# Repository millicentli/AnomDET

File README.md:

# AnomDET
Anomaly Detection @ UW

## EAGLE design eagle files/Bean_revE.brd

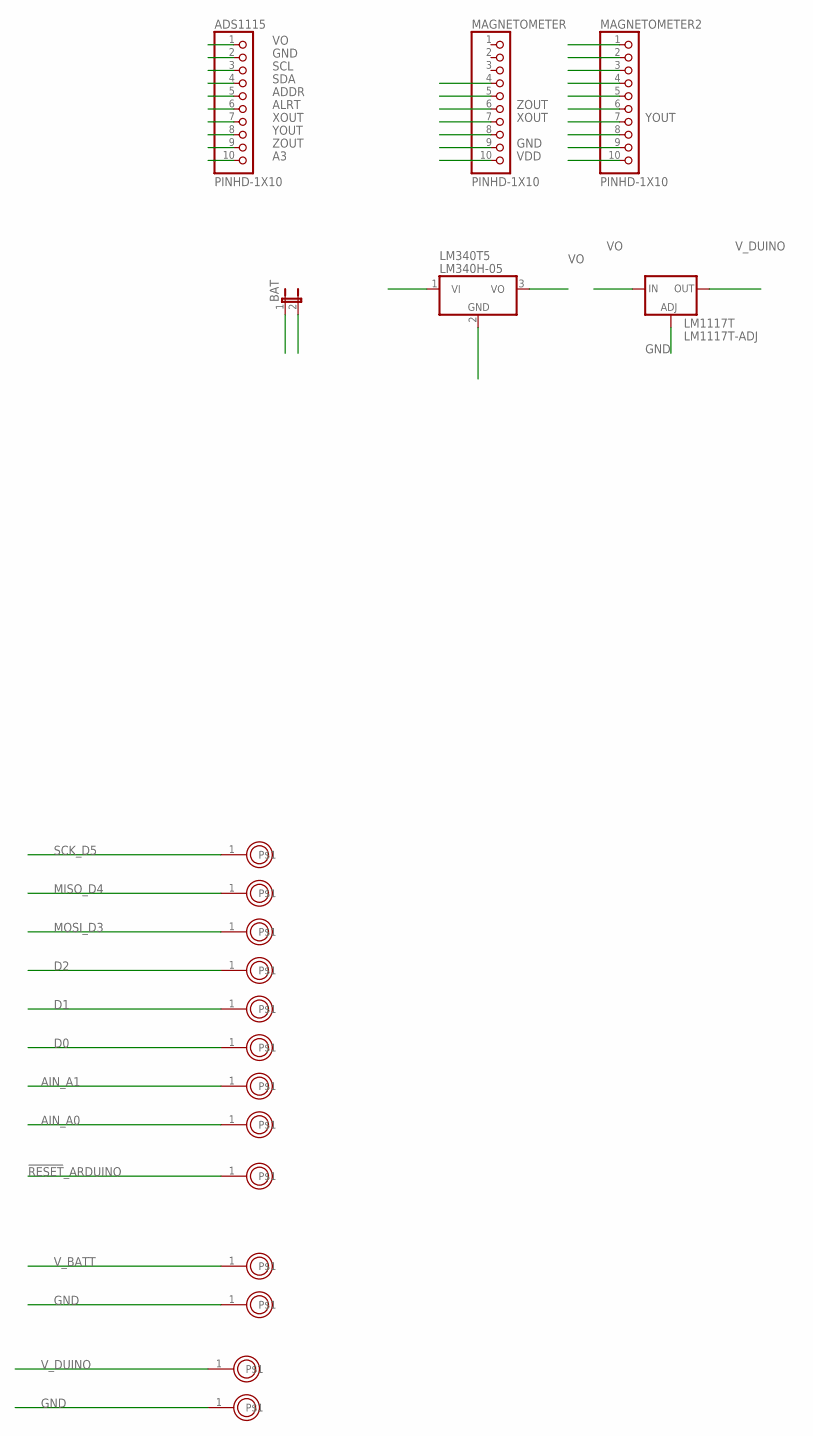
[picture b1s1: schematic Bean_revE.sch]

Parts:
ADS1115: PINHD-1X10; 1X10-BIG
BAT: JP1E; JP1
LM340T5: LM340H-05; TO220H
LM1117T: LM1117T-ADJ; TO220
MAGNETOMETER, MAGNETOMETER2: PINHD-1X10; 1X10-BIG
U$1, U$3, U$4, U$5, U$6, U$7, U$8, U$9, U$10, U$45, U$46, U$52, U$53: PROTO_POINT; 1X01

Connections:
!RESET!_ARDUINO: U$46.1
A3: ADS1115.10
ADDR: ADS1115.5
AIN_A0: U$10.1
AIN_A1: U$9.1
ALRT: ADS1115.6
D0: U$8.1
D1: U$7.1
D2: U$6.1
GND: ADS1115.2, BAT.2, LM340T5.2 (GND), LM1117T.1 (ADJ), MAGNETOMETER.9, U$45.1, U$53.1
MISO_D4: U$4.1
MOSI_D3: U$5.1
SCK_D5: U$3.1
SCL: ADS1115.3
SDA: ADS1115.4
VDD: MAGNETOMETER.10
VI: BAT.1, LM340T5.1 (VI)
VO: ADS1115.1, LM340T5.3 (VO), LM1117T.3 (IN)
V_BATT: U$52.1
V_DUINO: LM1117T.2 (OUT), U$1.1
XOUT: ADS1115.7, MAGNETOMETER.7
YOUT: ADS1115.8, MAGNETOMETER2.7
ZOUT: ADS1115.9, MAGNETOMETER.6

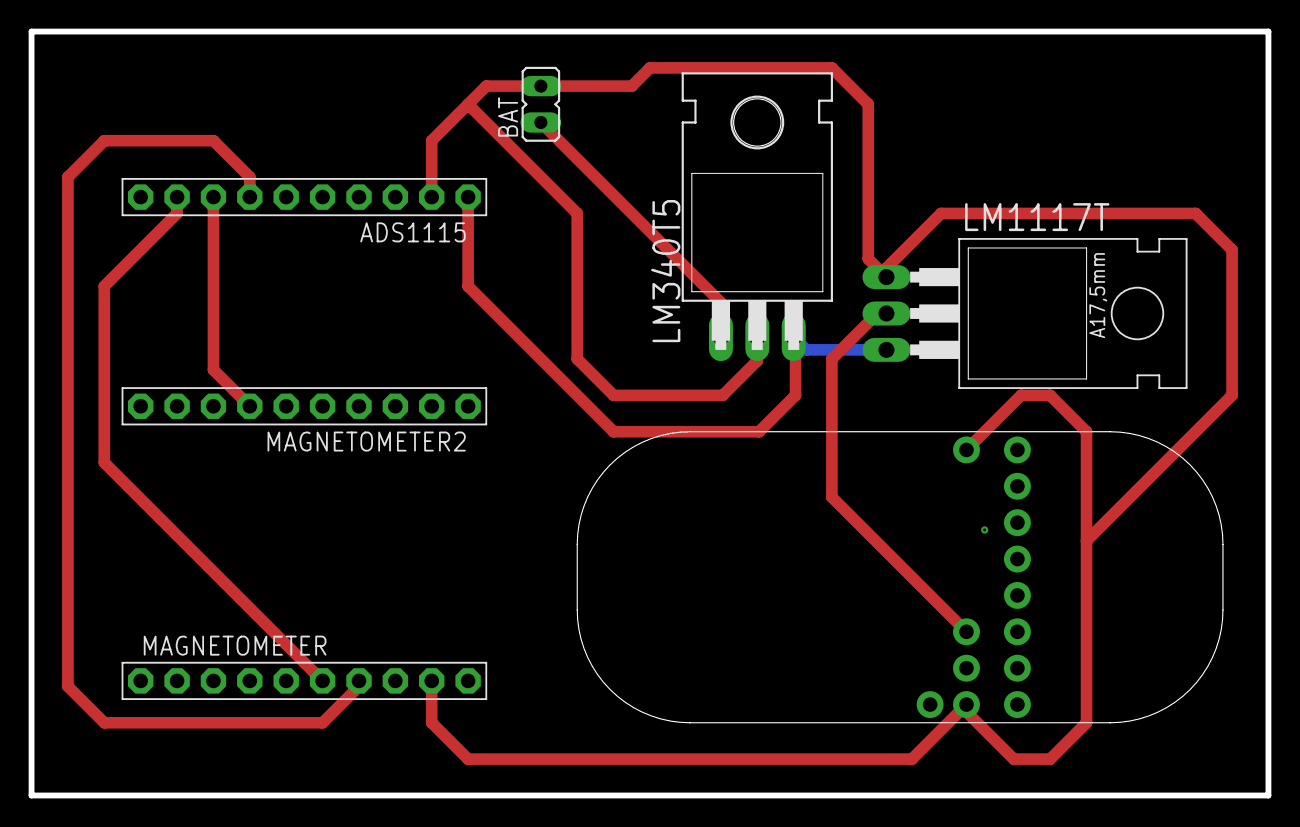
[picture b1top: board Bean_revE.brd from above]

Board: 2 copper layers, 86.4 x 53.3 mm, 19 parts (0 on the bottom side), 7 nets.

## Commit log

2016-07-25 added custom lib for ADS1115
2016-07-25 added arduino script
2016-08-19 graphs data that 3 points
2016-08-19 graphs data with 3 different data points
2016-08-19 Revert "graphs data that 3 points"
    This reverts commit d6aed7549bb0f116a16707e15b3c534a23da6640.
2016-08-19 Revert "graphs data with 3 different data points"
    This reverts commit 23349c42e913a750fdd9ff5776d25d202403ef46.
2016-08-19 graphs data with 3 points (x,y,z)
2016-08-19 graphs data converted from bytes over serial
2016-08-19 Added Python Scripts Folder
2016-08-19 Revert "added arduino script"
    This reverts commit da711c1f08d25ca4060434c88087c3f84ef19a16.
2016-08-19 added temperature (DS18x20) script for arduino
    requires DallasTemperature and OneWire library
2016-08-19 magnetometer test sent via int
2016-08-19 magnetometer test sent via bytes
2016-08-19 adc arduino script
2016-08-19 Revert "Added Python Scripts Folder"
    This reverts commit 87953e6d80f0fcb0324e27bc35f4bb245618730f.
2016-08-19 Python graphing scripts
2016-08-19 eagle files for board
